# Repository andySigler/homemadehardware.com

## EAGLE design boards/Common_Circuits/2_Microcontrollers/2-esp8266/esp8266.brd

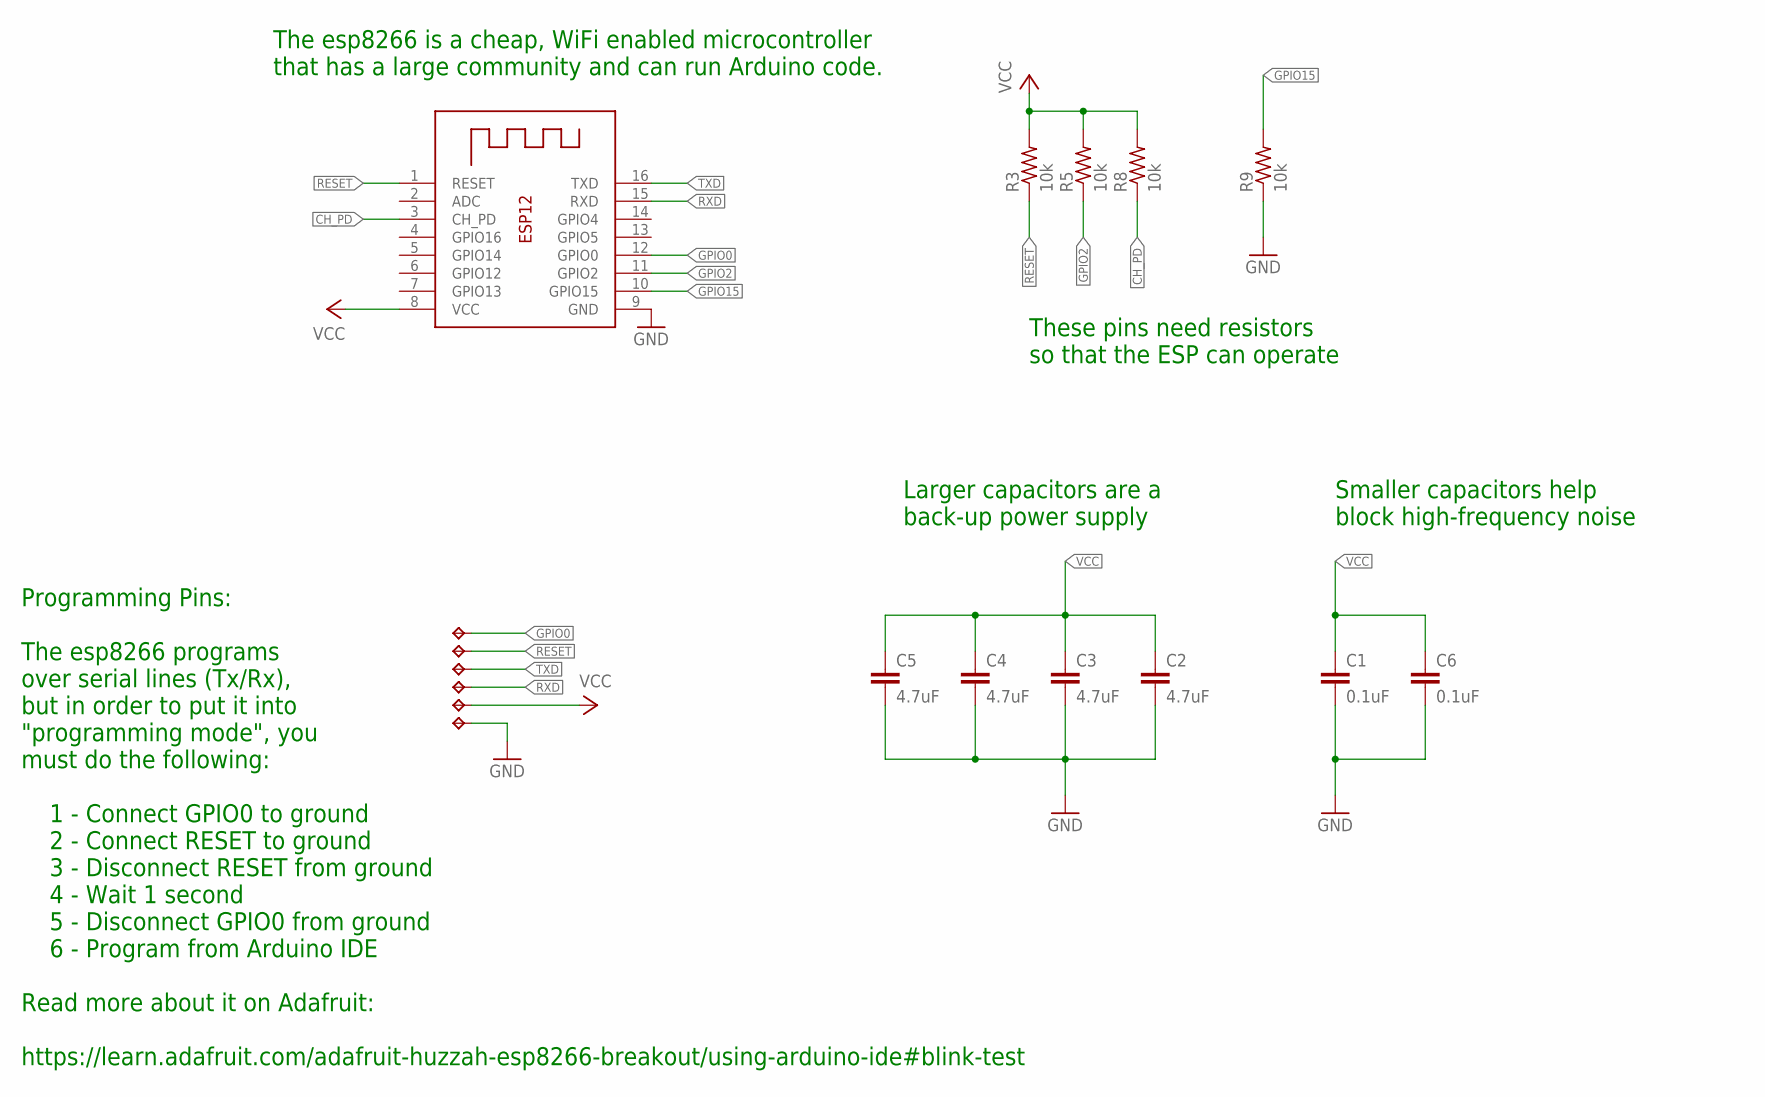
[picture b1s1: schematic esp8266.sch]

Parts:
C1, C6: 0.1uF; 0603
C2, C3, C4, C5: 4.7uF; 0603
GND: TPTP20R; TP20R
GPIO0: TPTP20R; TP20R
R3, R5, R8, R9: 10k; R0603
RESET: TPTP20R; TP20R
RX: TPTP20R; TP20R
TX: TPTP20R; TP20R
VCC: TPTP20R; TP20R
X1: ESP-12

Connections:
CH_PD: R8.1, X1.3 (CH_PD)
GND: C1.2, C2.2, C3.2, C4.2, C5.2, C6.2, GND.TP, R9.1, X1.9 (GND)
GPIO0: GPIO0.TP, X1.12 (GPIO0)
GPIO2: R5.1, X1.11 (GPIO2)
GPIO15: R9.2, X1.10 (GPIO15)
RESET: R3.1, RESET.TP, X1.1 (RESET)
RXD: RX.TP, X1.15 (RXD)
TXD: TX.TP, X1.16 (TXD)
VCC: C1.1, C2.1, C3.1, C4.1, C5.1, C6.1, R3.2, R5.2, R8.2, VCC.TP, X1.8 (VCC)

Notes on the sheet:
These pins need resistors so that the ESP can operate
The esp8266 is a cheap, WiFi enabled microcontroller that has a large community and can run Arduino code.
Programming Pins: The esp8266 programs over serial lines (Tx/Rx), but in order to put it into "programming mode", you must do the following: 1 - Connect GPIO0 to ground 2 - Connect RESET to ground 3 - Disconnect RESET from ground 4 - Wait 1 second 5 - Disconnect GPIO0 from ground 6 - Program from A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
Smaller capacitors help block high-frequency noise
Larger capacitors are a back-up power supply

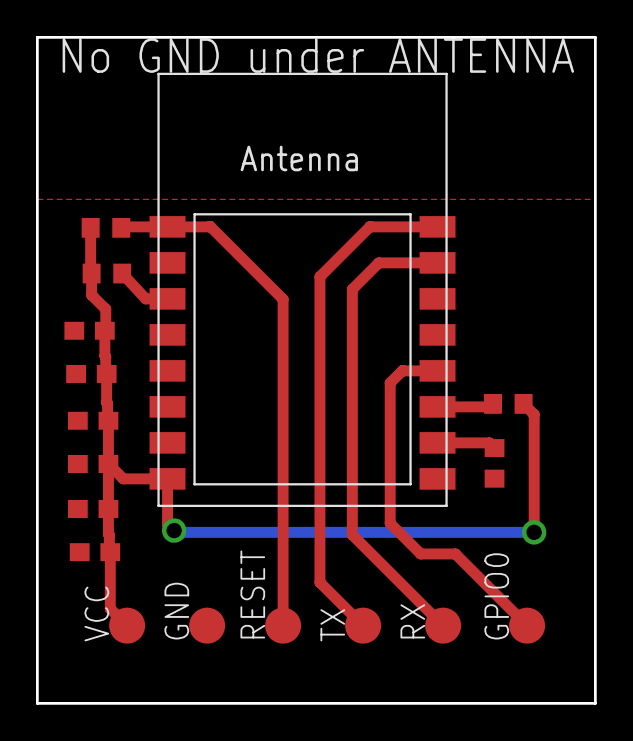
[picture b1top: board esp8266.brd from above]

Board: 2 copper layers, 31.0 x 37.0 mm, 17 parts (0 on the bottom side), 9 nets.

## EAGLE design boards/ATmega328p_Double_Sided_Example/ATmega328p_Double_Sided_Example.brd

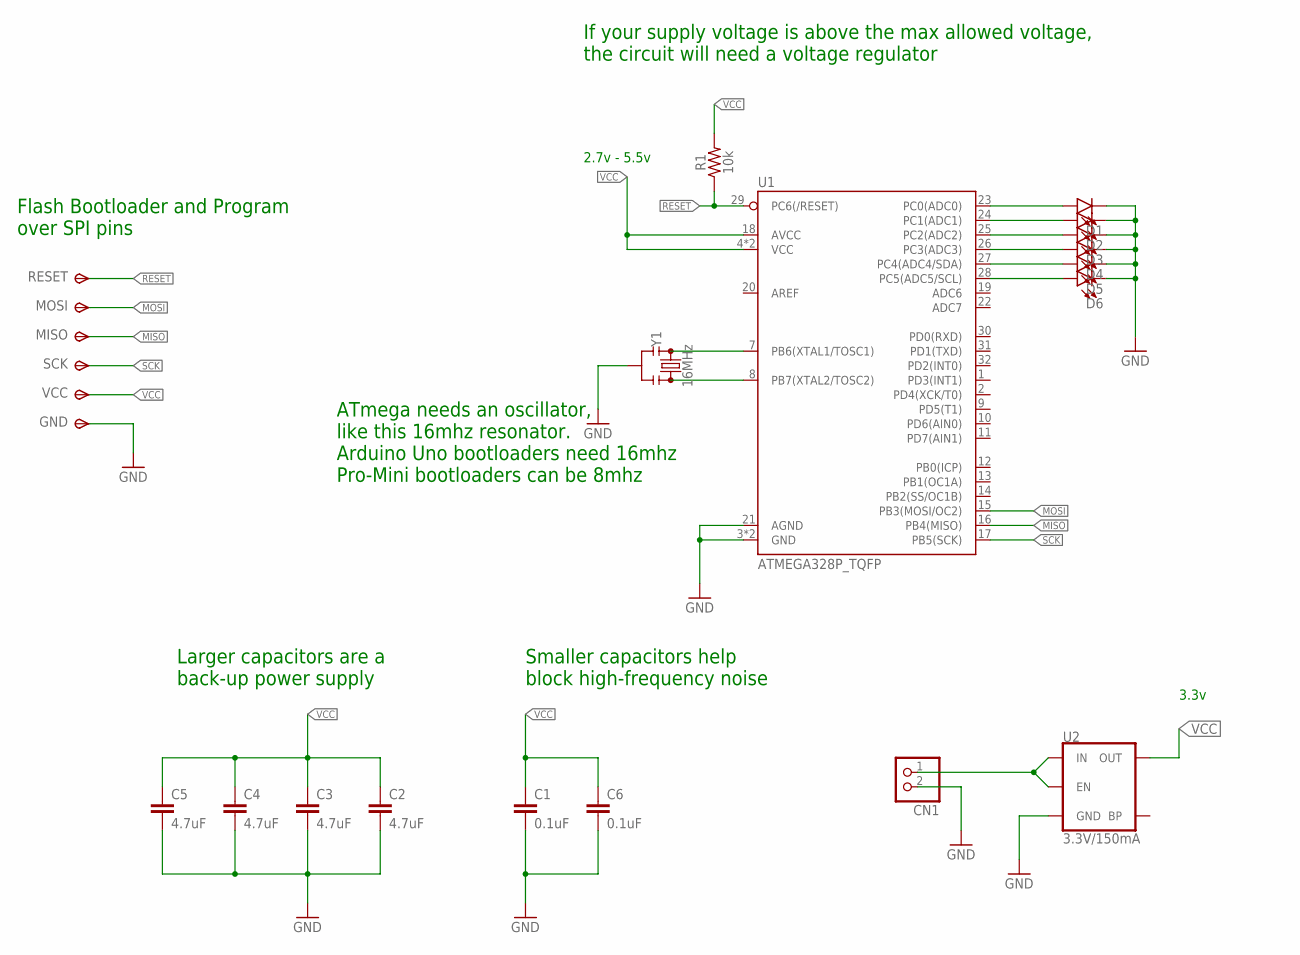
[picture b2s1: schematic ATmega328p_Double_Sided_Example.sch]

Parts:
C1, C6: 0.1uF; 0603
C2, C3, C4, C5: 4.7uF; 0603
CN1: JST_2PIN-SMT-RA; JST-PH-2-SMT-RA
D1, D2, D3, D4, D5, D6: LED0603; LED-0603
GND: TPSTP14SQ; TP14SQ
MISO: TPSTP14SQ; TP14SQ
MOSI: TPSTP14SQ; TP14SQ
R1: 10k; 0603
RESET: TPSTP14SQ; TP14SQ
SCK: TPSTP14SQ; TP14SQ
U1: ATMEGA328P_TQFP; TQFP32-08
U2: 3.3V/150mA; SOT23-5
VCC: TPSTP14SQ; TP14SQ
Y1: 16MHz; RESONATOR-SMD-3.2X1.3

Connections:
GND: C1.2, C2.2, C3.2, C4.2, C5.2, C6.2, CN1.2 (1), D1.C, D2.C, D3.C, D4.C, D5.C, D6.C, GND.TP, U1.3 (GND), U1.5 (GND), U1.21 (AGND), U2.2 (GND), Y1.2
MISO: MISO.TP, U1.16 (PB4(MISO))
MOSI: MOSI.TP, U1.15 (PB3(MOSI/OC2))
unnamed: CN1.1 (2), U2.1 (IN), U2.3 (EN)
unnamed: U1.7 (PB6(XTAL1/TOSC1)), Y1.1
unnamed: U1.8 (PB7(XTAL2/TOSC2)), Y1.3
unnamed: D1.A, U1.23 (PC0(ADC0))
unnamed: D2.A, U1.24 (PC1(ADC1))
unnamed: D3.A, U1.25 (PC2(ADC2))
unnamed: D4.A, U1.26 (PC3(ADC3))
unnamed: D5.A, U1.27 (PC4(ADC4/SDA))
unnamed: D6.A, U1.28 (PC5(ADC5/SCL))
RESET: R1.1, RESET.TP, U1.29 (PC6(/RESET))
SCK: SCK.TP, U1.17 (PB5(SCK))
VCC: C1.1, C2.1, C3.1, C4.1, C5.1, C6.1, R1.2, U1.4 (VCC), U1.6 (VCC), U1.18 (AVCC), U2.5 (OUT), VCC.TP

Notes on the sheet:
2.7v - 5.5v
Flash Bootloader and Program over SPI pins
If your supply voltage is above the max allowed voltage, the circuit will need a voltage regulator
Smaller capacitors help block high-frequency noise
Larger capacitors are a back-up power supply
ATmega needs an oscillator, like this 16mhz resonator. Arduino Uno bootloaders need 16mhz Pro-Mini bootloaders can be 8mhz
3.3v

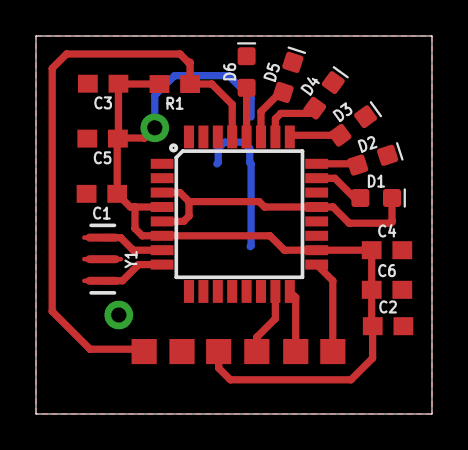
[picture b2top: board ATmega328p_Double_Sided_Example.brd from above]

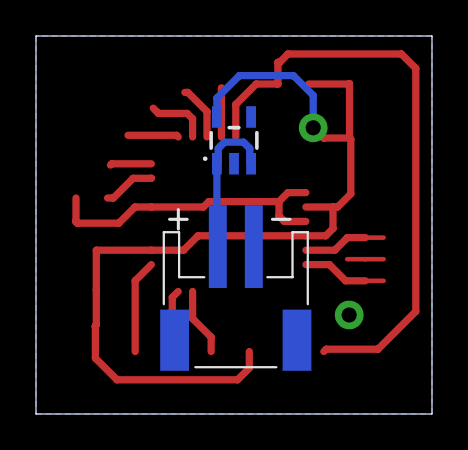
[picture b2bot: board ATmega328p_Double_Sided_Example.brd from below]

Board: 2 copper layers, 22.0 x 21.0 mm, 23 parts (2 on the bottom side), 15 nets.

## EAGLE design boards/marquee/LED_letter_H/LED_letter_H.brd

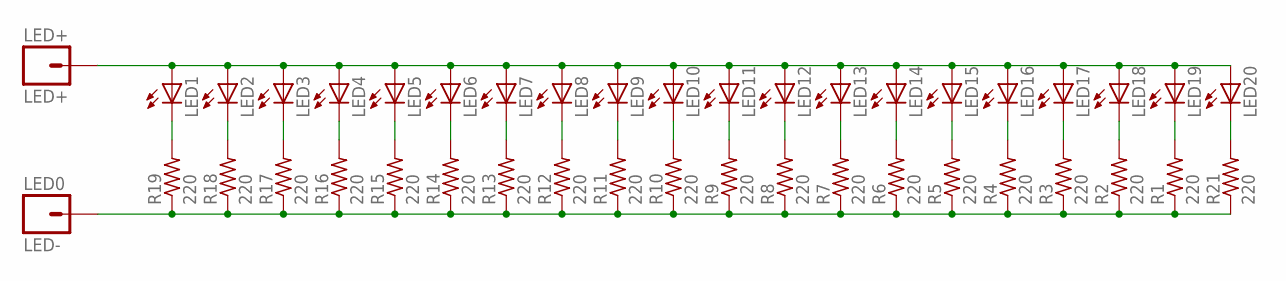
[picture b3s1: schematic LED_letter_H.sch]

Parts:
LED0: LED-; 1X01_OFFSET
LED1, LED2, LED3, LED4, LED5, LED6, LED7, LED8, LED9, LED10, LED11, LED12, LED13, LED14, LED15, LED16, LED17, LED18, LED19, LED20: LED5MM
LED+: LED+; 1X01_OFFSET
R1, R2, R3, R4, R5, R6, R7, R8, R9, R10, R11, R12, R13, R14, R15, R16, R17, R18, R19, R21: 220; 0207/10

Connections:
+: LED1.A, LED2.A, LED3.A, LED4.A, LED5.A, LED6.A, LED7.A, LED8.A, LED9.A, LED10.A, LED11.A, LED12.A, LED13.A, LED14.A, LED15.A, LED16.A, LED17.A, LED18.A, LED19.A, LED20.A, LED+.1
-: LED0.1, R1.1, R2.1, R3.1, R4.1, R5.1, R6.1, R7.1, R8.1, R9.1, R10.1, R11.1, R12.1, R13.1, R14.1, R15.1, R16.1, R17.1, R18.1, R19.1, R21.1
unnamed: LED1.K (C), R19.2
unnamed: LED20.K (C), R21.2
unnamed: LED19.K (C), R1.2
unnamed: LED18.K (C), R2.2
unnamed: LED17.K (C), R3.2
unnamed: LED16.K (C), R4.2
unnamed: LED15.K (C), R5.2
unnamed: LED14.K (C), R6.2
unnamed: LED13.K (C), R7.2
unnamed: LED12.K (C), R8.2
unnamed: LED11.K (C), R9.2
unnamed: LED10.K (C), R10.2
unnamed: LED9.K (C), R11.2
unnamed: LED8.K (C), R12.2
unnamed: LED7.K (C), R13.2
unnamed: LED6.K (C), R14.2
unnamed: LED5.K (C), R15.2
unnamed: LED4.K (C), R16.2
unnamed: LED3.K (C), R17.2
unnamed: LED2.K (C), R18.2

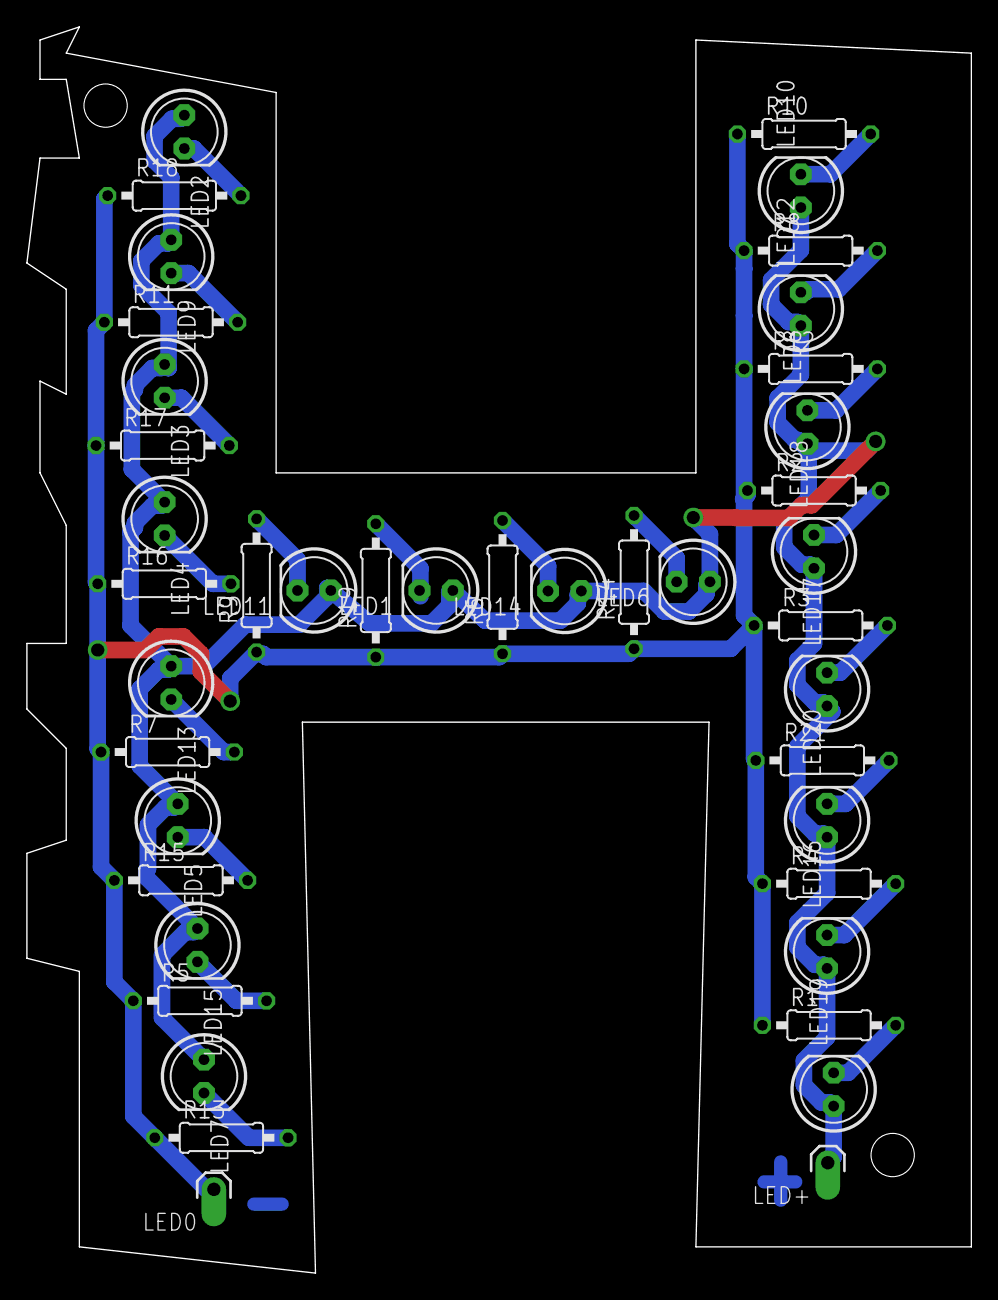
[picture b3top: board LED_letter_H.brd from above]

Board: 2 copper layers, 72.0 x 95.0 mm, 42 parts (0 on the bottom side), 22 nets.

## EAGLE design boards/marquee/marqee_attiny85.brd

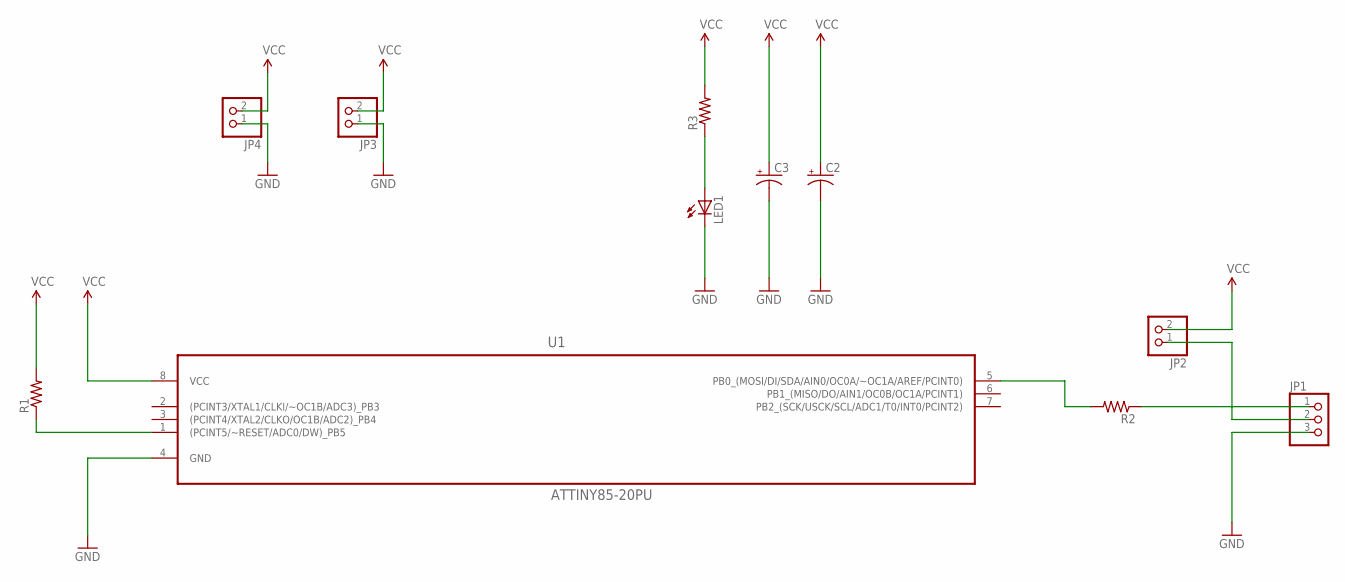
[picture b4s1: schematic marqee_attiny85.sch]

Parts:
C2, C3: CPOL-USE5-8.5; E5-8,5
JP1: PINHD-1X3; 1X03
JP2, JP3, JP4: PINHD-1X2; 1X02
LED1: LED5MM
R1, R2, R3: R-US_0207/10; 0207/10
U1: ATTINY85-20PU; DIP254P762X533-8

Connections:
GND: C2.-, C3.-, JP1.3, JP3.1, JP4.1, LED1.K (C), U1.4 (GND)
unnamed: R1.1, U1.1 ((PCINT5/~RESET/ADC0/DW)_PB5)
unnamed: JP1.1, R2.1
unnamed: LED1.A, R3.1
unnamed: R2.2, U1.5 (PB0_(MOSI/DI/SDA/AIN0/OC0A/~OC1A/AREF/P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)
unnamed: JP1.2, JP2.1
VCC: C2.+, C3.+, JP2.2, JP3.2, JP4.2, R1.2, R3.2, U1.8 (VCC)

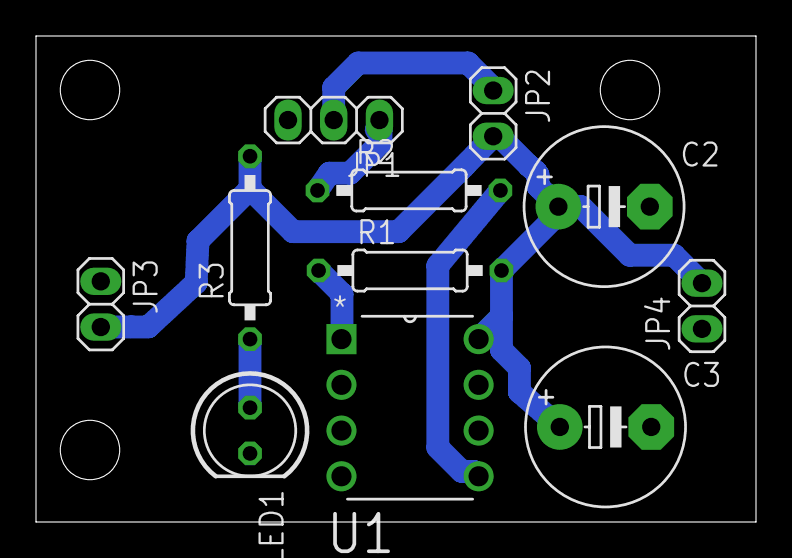
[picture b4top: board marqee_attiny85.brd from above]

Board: 2 copper layers, 40.0 x 27.0 mm, 11 parts (0 on the bottom side), 7 nets.

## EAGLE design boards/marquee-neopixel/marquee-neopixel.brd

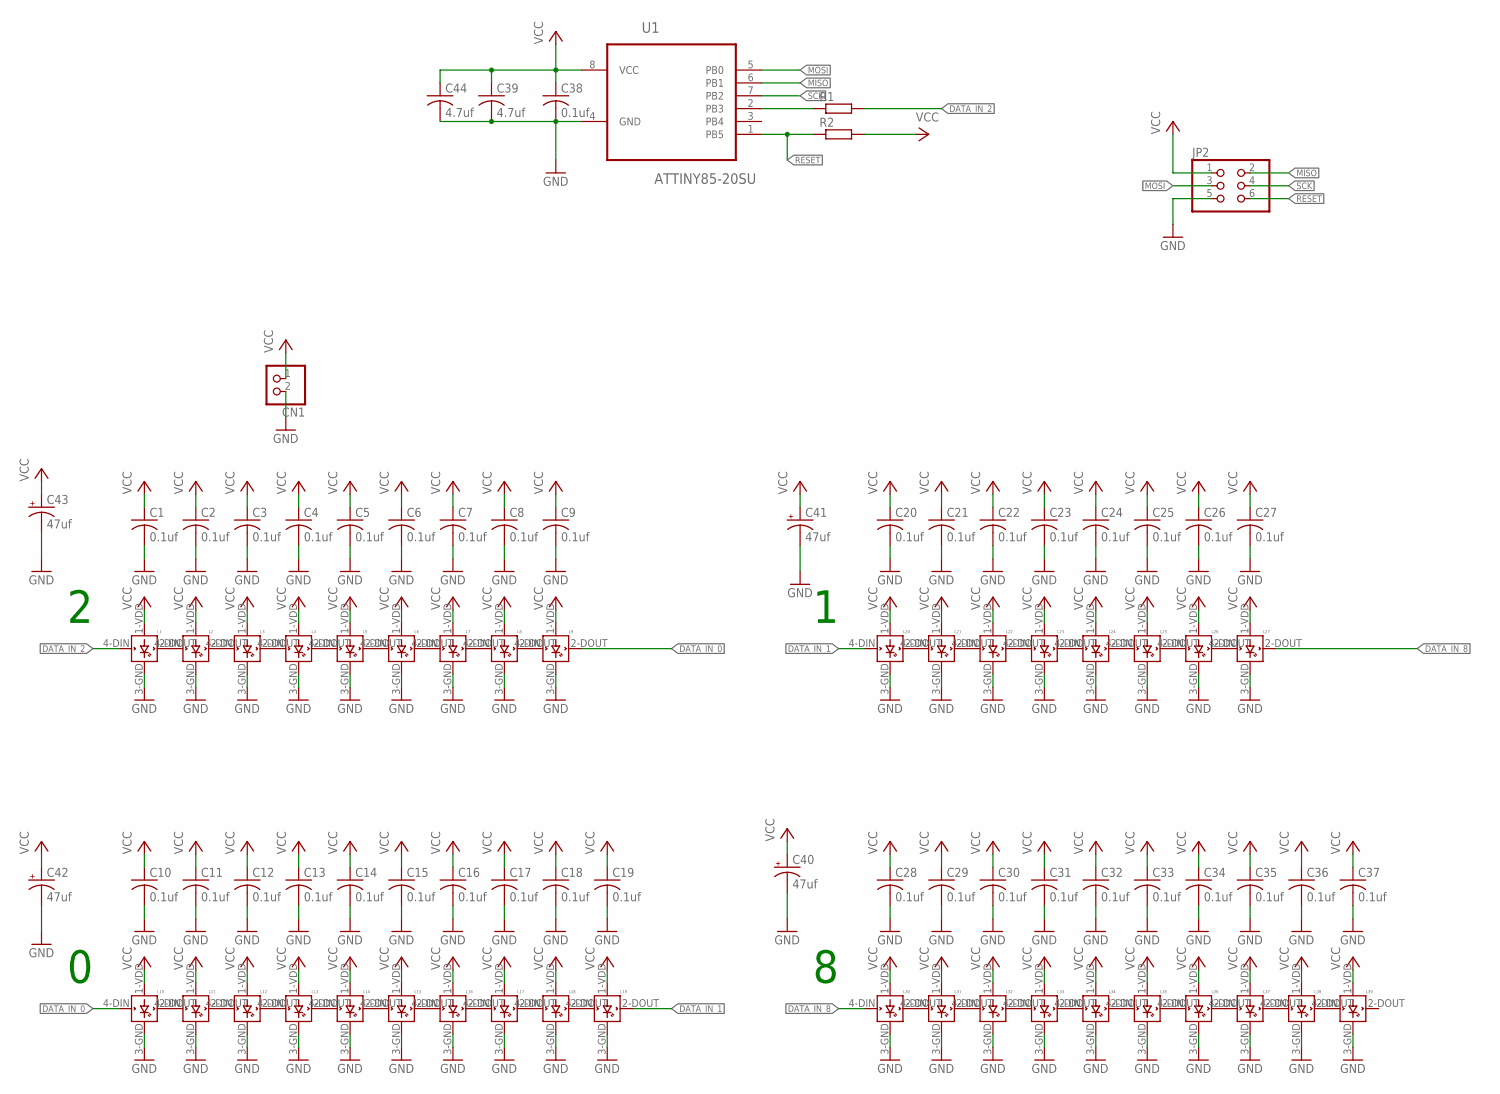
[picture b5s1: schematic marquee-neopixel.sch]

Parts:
C1, C2, C3, C4, C5, C6, C7, C8, C9, C10, C11, C12, C13, C14, C15, C16, C17, C18, C19, C20, C21, C22, C23, C24, C25, C26, C27, C28, C29, C30, C31, C32, C33, C34, C35, C36, C37, C38: 0.1uf; C0603
C39, C44: 4.7uf; C0603
C40, C41, C42, C43: 47uf; 153CLV-0605
CN1: JST_2PIN-SMT-RA; JST-PH-2-SMT-RA
JP2: PINHD-2X3; 2X03
L1, L2, L3, L4, L5, L6, L7, L8, L9, L10, L11, L12, L13, L14, L15, L16, L17, L18, L19, L20, L21, L22, L23, L24, L25, L26, L27, L30, L31, L32, L33, L34, L35, L36, L37, L38, L39: WS2812B
R1, R2: RR0603; R0603
U1: ATTINY85-20SU; SOIC127P798X216-8N

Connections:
DATA_IN_0: L9.2-DOUT (DOUT), L10.4-DIN (DIN)
DATA_IN_1: L19.2-DOUT (DOUT), L20.4-DIN (DIN)
DATA_IN_2: L1.4-DIN (DIN), R1.2
DATA_IN_8: L27.2-DOUT (DOUT), L30.4-DIN (DIN)
GND: C1.2, C2.2, C3.2, C4.2, C5.2, C6.2, C7.2, C8.2, C9.2, C10.2, C11.2, C12.2, C13.2, C14.2, C15.2, C16.2, C17.2, C18.2, C19.2, C20.2, C21.2, C22.2, C23.2, C24.2, C25.2, C26.2, C27.2, C28.2, C29.2, C30.2, C31.2, C32.2, C33.2, C34.2, C35.2, C36.2, C37.2, C38.2, C39.2, C40.-, C41.-, C42.-, C43.-, C44.2, CN1.2 (1), JP2.5, L1.3-GND (GND), L2.3-GND (GND), L3.3-GND (GND), L4.3-GND (GND), L5.3-GND (GND), L6.3-GND (GND), L7.3-GND (GND), L8.3-GND (GND), L9.3-GND (GND), L10.3-GND (GND), L11.3-GND (GND), L12.3-GND (GND), L13.3-GND (GND), L14.3-GND (GND), L15.3-GND (GND), L16.3-GND (GND), L17.3-GND (GND), L18.3-GND (GND), L19.3-GND (GND), L20.3-GND (GND), L21.3-GND (GND), L22.3-GND (GND), L23.3-GND (GND), L24.3-GND (GND), L25.3-GND (GND), L26.3-GND (GND), L27.3-GND (GND), L30.3-GND (GND), L31.3-GND (GND), L32.3-GND (GND), L33.3-GND (GND), L34.3-GND (GND), L35.3-GND (GND), L36.3-GND (GND), L37.3-GND (GND), L38.3-GND (GND), L39.3-GND (GND), U1.4 (GND)
MISO: JP2.2, U1.6 (PB1)
MOSI: JP2.3, U1.5 (PB0)
unnamed: L1.2-DOUT (DOUT), L2.4-DIN (DIN)
unnamed: L2.2-DOUT (DOUT), L3.4-DIN (DIN)
unnamed: L3.2-DOUT (DOUT), L4.4-DIN (DIN)
unnamed: L4.2-DOUT (DOUT), L5.4-DIN (DIN)
unnamed: L5.2-DOUT (DOUT), L6.4-DIN (DIN)
unnamed: L6.2-DOUT (DOUT), L7.4-DIN (DIN)
unnamed: L7.2-DOUT (DOUT), L8.4-DIN (DIN)
unnamed: L8.2-DOUT (DOUT), L9.4-DIN (DIN)
unnamed: L10.2-DOUT (DOUT), L11.4-DIN (DIN)
unnamed: L11.2-DOUT (DOUT), L12.4-DIN (DIN)
unnamed: L12.2-DOUT (DOUT), L13.4-DIN (DIN)
unnamed: L13.2-DOUT (DOUT), L14.4-DIN (DIN)
unnamed: L14.2-DOUT (DOUT), L15.4-DIN (DIN)
unnamed: L15.2-DOUT (DOUT), L16.4-DIN (DIN)
unnamed: L16.2-DOUT (DOUT), L17.4-DIN (DIN)
unnamed: L17.2-DOUT (DOUT), L18.4-DIN (DIN)
unnamed: L18.2-DOUT (DOUT), L19.4-DIN (DIN)
unnamed: L20.2-DOUT (DOUT), L21.4-DIN (DIN)
unnamed: L21.2-DOUT (DOUT), L22.4-DIN (DIN)
unnamed: L22.2-DOUT (DOUT), L23.4-DIN (DIN)
unnamed: L23.2-DOUT (DOUT), L24.4-DIN (DIN)
unnamed: L24.2-DOUT (DOUT), L25.4-DIN (DIN)
unnamed: L25.2-DOUT (DOUT), L26.4-DIN (DIN)
unnamed: L26.2-DOUT (DOUT), L27.4-DIN (DIN)
unnamed: R1.1, U1.2 (PB3)
unnamed: L30.2-DOUT (DOUT), L31.4-DIN (DIN)
unnamed: L31.2-DOUT (DOUT), L32.4-DIN (DIN)
unnamed: L32.2-DOUT (DOUT), L33.4-DIN (DIN)
unnamed: L33.2-DOUT (DOUT), L34.4-DIN (DIN)
unnamed: L34.2-DOUT (DOUT), L35.4-DIN (DIN)
unnamed: L35.2-DOUT (DOUT), L36.4-DIN (DIN)
unnamed: L36.2-DOUT (DOUT), L37.4-DIN (DIN)
unnamed: L37.2-DOUT (DOUT), L38.4-DIN (DIN)
unnamed: L38.2-DOUT (DOUT), L39.4-DIN (DIN)
RESET: JP2.6, R2.1, U1.1 (PB5)
SCK: JP2.4, U1.7 (PB2)
VCC: C1.1, C2.1, C3.1, C4.1, C5.1, C6.1, C7.1, C8.1, C9.1, C10.1, C11.1, C12.1, C13.1, C14.1, C15.1, C16.1, C17.1, C18.1, C19.1, C20.1, C21.1, C22.1, C23.1, C24.1, C25.1, C26.1, C27.1, C28.1, C29.1, C30.1, C31.1, C32.1, C33.1, C34.1, C35.1, C36.1, C37.1, C38.1, C39.1, C40.+, C41.+, C42.+, C43.+, C44.1, CN1.1 (2), JP2.1, L1.1-VDD (VDD), L2.1-VDD (VDD), L3.1-VDD (VDD), L4.1-VDD (VDD), L5.1-VDD (VDD), L6.1-VDD (VDD), L7.1-VDD (VDD), L8.1-VDD (VDD), L9.1-VDD (VDD), L10.1-VDD (VDD), L11.1-VDD (VDD), L12.1-VDD (VDD), L13.1-VDD (VDD), L14.1-VDD (VDD), L15.1-VDD (VDD), L16.1-VDD (VDD), L17.1-VDD (VDD), L18.1-VDD (VDD), L19.1-VDD (VDD), L20.1-VDD (VDD), L21.1-VDD (VDD), L22.1-VDD (VDD), L23.1-VDD (VDD), L24.1-VDD (VDD), L25.1-VDD (VDD), L26.1-VDD (VDD), L27.1-VDD (VDD), L30.1-VDD (VDD), L31.1-VDD (VDD), L32.1-VDD (VDD), L33.1-VDD (VDD), L34.1-VDD (VDD), L35.1-VDD (VDD), L36.1-VDD (VDD), L37.1-VDD (VDD), L38.1-VDD (VDD), L39.1-VDD (VDD), R2.2, U1.8 (VCC)

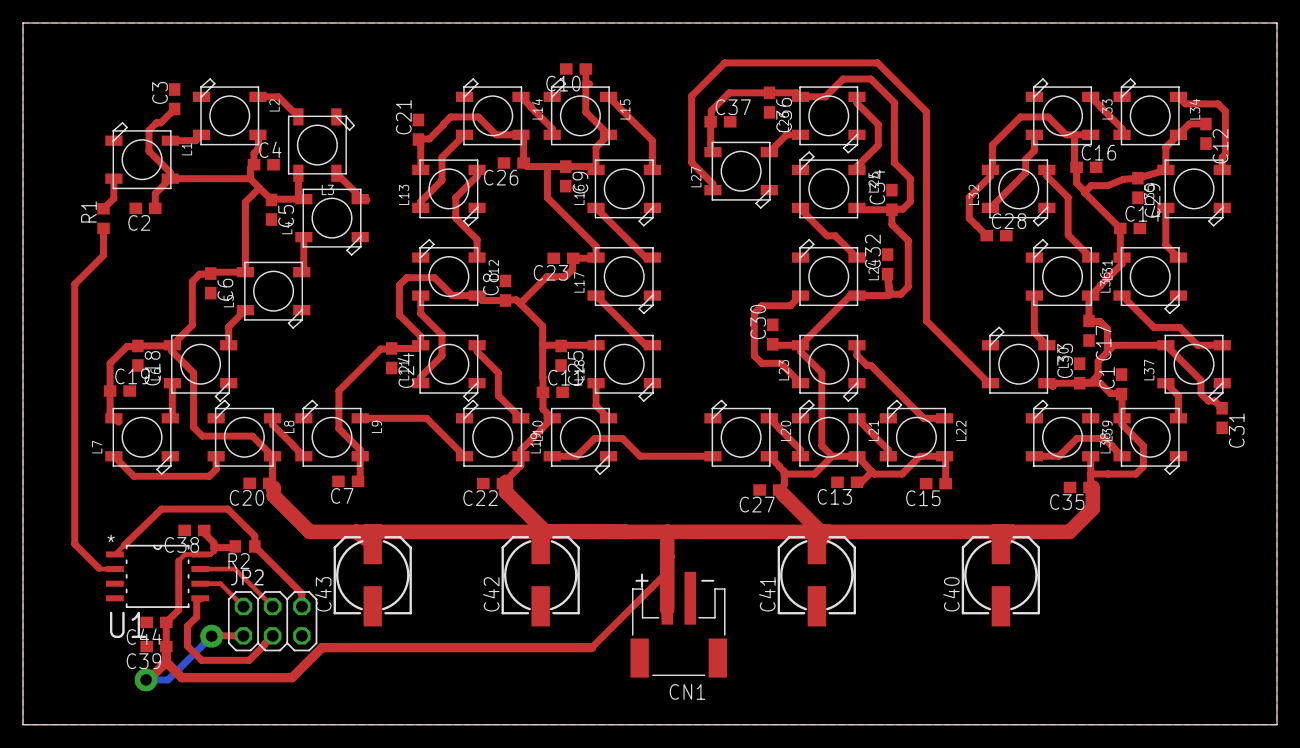
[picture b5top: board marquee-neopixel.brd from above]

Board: 2 copper layers, 109.0 x 61.0 mm, 86 parts (0 on the bottom side), 44 nets.

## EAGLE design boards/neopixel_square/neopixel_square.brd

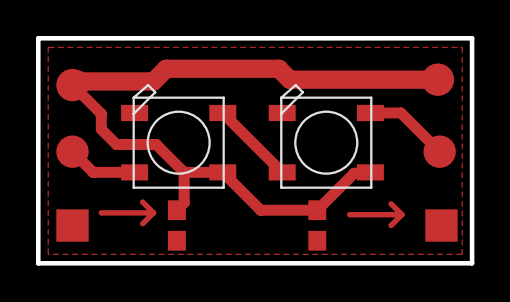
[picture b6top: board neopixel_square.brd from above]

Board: 2 copper layers, 24.1 x 12.5 mm, 10 parts (0 on the bottom side), 5 nets.

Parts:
C1, C9: 0.1uf; C0603
DATA, DATA1: TPTP18R; TP18R
GND: TPTP18SQ; TP18SQ
GROUND: TPTP18R; TP18R
L1, L9: WS2812B
POWER: TPTP18SQ; TP18SQ
VCC: TPTP18R; TP18R

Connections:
DATA_IN: DATA.TP, L9.4-DIN
DATA_OUT: DATA1.TP, L1.2-DOUT
GND: C1.2, C9.2, GND.TP, L1.3-GND, L9.3-GND, POWER.TP
unnamed: L1.4-DIN, L9.2-DOUT
VCC: C1.1, C9.1, GROUND.TP, L1.1-VDD, L9.1-VDD, VCC.TP

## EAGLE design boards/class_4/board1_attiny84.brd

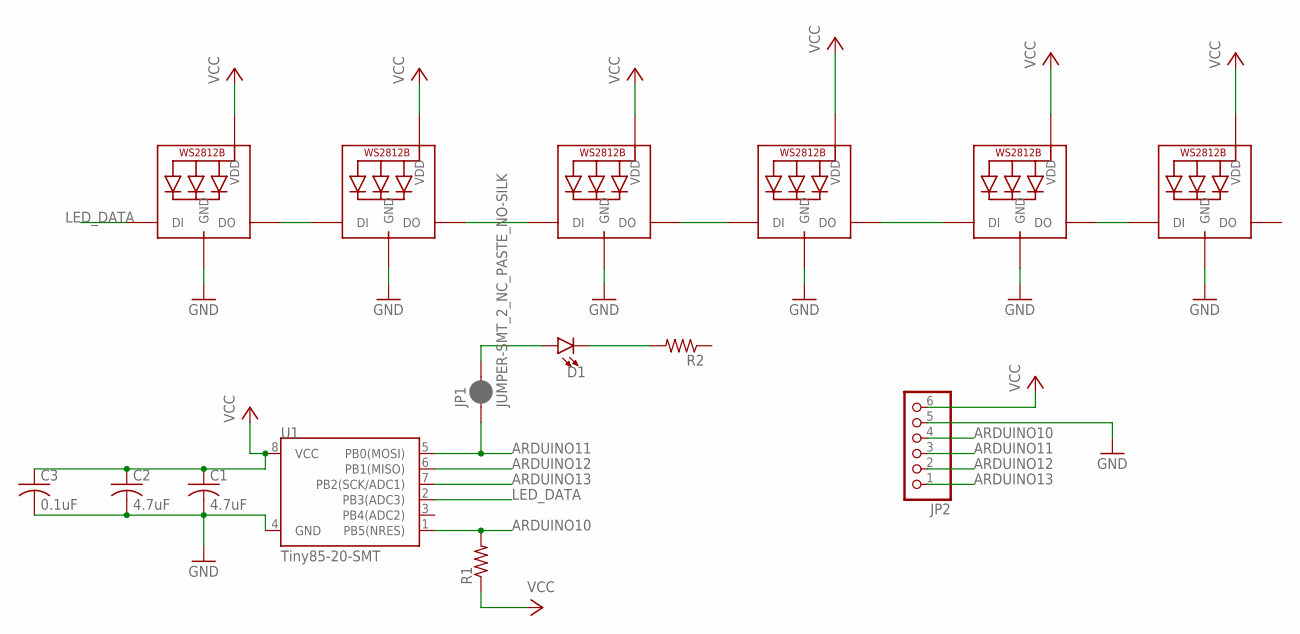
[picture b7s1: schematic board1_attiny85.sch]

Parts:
C1, C2: 4.7uF; C0603
C3: 0.1uF; C0603
D1: LED0603; LED-0603
JP1: JUMPER-SMT_2_NC_PASTE_NO-SILK; SMT-JUMPER_2_NC_PASTE_NO-SILK
JP2: PINHD-1X6; 1X06
LED1, LED2, LED3, LED4, LED5, LED6: WS2812B5050; WS2812B
R1, R2: R-US_R0603; R0603
U1: Tiny85-20-SMT; SO08-EIAJ_MCU

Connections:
ARDUINO10: JP2.4, R1.2, U1.1 (PB5(NRES))
ARDUINO11: JP1.1, JP2.3, U1.5 (PB0(MOSI))
ARDUINO12: JP2.2, U1.6 (PB1(MISO))
ARDUINO13: JP2.1, U1.7 (PB2(SCK/ADC1))
GND: C1.2, C2.2, C3.2, JP2.5, LED1.3-GND (GND), LED2.3-GND (GND), LED3.3-GND (GND), LED4.3-GND (GND), LED5.3-GND (GND), LED6.3-GND (GND), U1.4 (GND)
LED_DATA: LED1.4-DIN (DI), U1.2 (PB3(ADC3))
unnamed: LED1.2-DOUT (DO), LED2.4-DIN (DI)
unnamed: D1.C, R2.2
unnamed: D1.A, JP1.2
unnamed: LED2.2-DOUT (DO), LED3.4-DIN (DI)
unnamed: LED3.2-DOUT (DO), LED4.4-DIN (DI)
unnamed: LED4.2-DOUT (DO), LED5.4-DIN (DI)
unnamed: LED5.2-DOUT (DO), LED6.4-DIN (DI)
VCC: C1.1, C2.1, C3.1, JP2.6, LED1.1-VDD (VDD), LED2.1-VDD (VDD), LED3.1-VDD (VDD), LED4.1-VDD (VDD), LED5.1-VDD (VDD), LED6.1-VDD (VDD), R1.1, U1.8 (VCC)

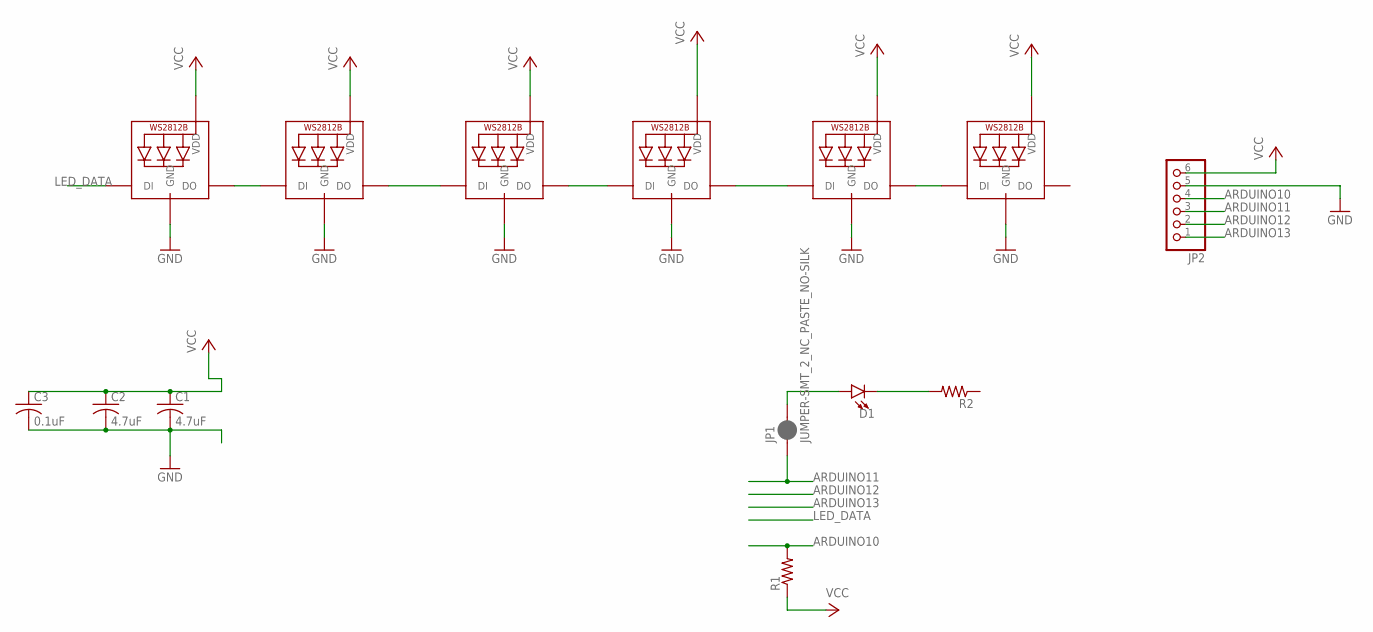
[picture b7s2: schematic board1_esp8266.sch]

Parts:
C1, C2: 4.7uF; C0603
C3: 0.1uF; C0603
D1: LED0603; LED-0603
JP1: JUMPER-SMT_2_NC_PASTE_NO-SILK; SMT-JUMPER_2_NC_PASTE_NO-SILK
JP2: PINHD-1X6; 1X06
LED1, LED2, LED3, LED4, LED5, LED6: WS2812B5050; WS2812B
R1, R2: R-US_R0603; R0603

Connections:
ARDUINO10: JP2.4, R1.2; also elsewhere on the board
ARDUINO11: JP1.1, JP2.3; also elsewhere on the board
ARDUINO12: JP2.2; also elsewhere on the board
ARDUINO13: JP2.1; also elsewhere on the board
GND: C1.2, C2.2, C3.2, JP2.5, LED1.3-GND (GND), LED2.3-GND (GND), LED3.3-GND (GND), LED4.3-GND (GND), LED5.3-GND (GND), LED6.3-GND (GND); also elsewhere on the board
LED_DATA: LED1.4-DIN (DI); also elsewhere on the board
unnamed: LED1.2-DOUT (DO), LED2.4-DIN (DI)
unnamed: D1.C, R2.2
unnamed: D1.A, JP1.2
unnamed: LED2.2-DOUT (DO), LED3.4-DIN (DI)
unnamed: LED3.2-DOUT (DO), LED4.4-DIN (DI)
unnamed: LED4.2-DOUT (DO), LED5.4-DIN (DI)
unnamed: LED5.2-DOUT (DO), LED6.4-DIN (DI)
VCC: C1.1, C2.1, C3.1, JP2.6, LED1.1-VDD (VDD), LED2.1-VDD (VDD), LED3.1-VDD (VDD), LED4.1-VDD (VDD), LED5.1-VDD (VDD), LED6.1-VDD (VDD), R1.1; also elsewhere on the board

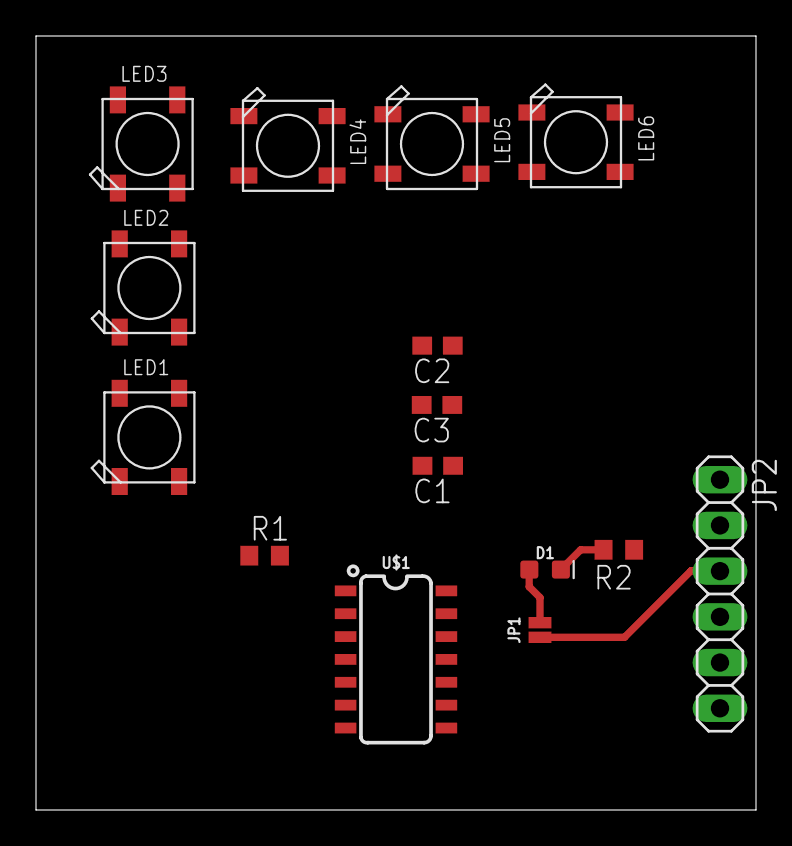
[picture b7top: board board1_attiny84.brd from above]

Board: 2 copper layers, 40.0 x 43.0 mm, 15 parts (0 on the bottom side), 11 nets.

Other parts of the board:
U$1: ATTINY84; SO14

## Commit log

2015-08-01 init commit
2015-08-01 added basic layout
2015-08-05 small updates before showing tom
2015-08-05 adsf
2015-08-09 reformatting and added lots of links
2015-08-09 asdf
2015-08-10 more content added to syllabus page
2015-08-13 updated Links page, maybe it's done
2015-08-13 added overview to syllabus page
2015-08-16 added prior projects and more stuff
2015-08-29 added more info to syllabus page
2015-08-29 created Examples page
2015-09-03 final update before class starts
2015-09-03 fixed andy's link
2015-09-04 added board manager links
2015-09-04 changed linked soldering iron to a cheaper one
2015-09-10 added student links, and fixed misspelled word
2015-09-10 added tinkersphere link
2015-09-10 added links to Eagle libraries
2015-09-10 new student link
2015-09-10 added more student links
2015-09-14 added eagle commands page
2015-09-14 updated students page
2015-09-22 removed waitlist student, and added board commands
2015-09-24 added vimeo tutorials to the links page
2015-09-24 updated dynamask link to be an eBay search term
2015-10-01 changed syllabus for class 5
2015-10-12 added new Processes page
2015-10-13 fixed heat gun temperature
2015-10-15 added roland to class 7 and processes page
2015-10-16 added new bit buying links to things page
2015-10-29 updated syllabus
2015-11-11 added new job to index and about pages
2015-11-13 updated links page to include wireless modules
2015-11-13 added PNP ulp to links folder
2015-12-03 small change
2017-01-23 adds .gitignore
2017-01-23 adds archives to hold 2015 class pages
2017-01-23 prepares website for Spring 2017 class
2017-01-24 starts adding lesson plans to each class on syllabus
2017-01-25 adds details to classes on syllabus page
2017-01-27 updates Things page with required tools to order
2017-01-27 adds archive html page and nav links
2017-01-27 adds link to examples from Michelle's course
2017-01-27 adds link to 8mhz internal board
2017-01-28 updates students page
2017-01-28 adds list of options for ordering out
2017-01-29 udates week 1 homework assignment
2017-01-29 add linkable ids to weeks
2017-01-29 fixes links
2017-01-29 adds PCB soldering video ink
2017-01-29 different solding link
2017-01-29 fixes links on old Examples page
2017-01-30 adds student link
2017-01-30 adds Common Sub-Circuits
2017-01-30 adds link to parts search engine
2017-02-03 updates some blog links
2017-02-03 adds missing student links
2017-02-04 updates class 2 homework, and updates eagle commands page
2017-02-04 adds video to syllabus page
2017-02-10 adds example boards for class 3
2017-02-10 udpdates student links
2017-02-10 updates example board to use pot
2017-02-11 adds class 3 video and updates drill bit link
2017-02-17 updates class 4 topics
2017-03-03 updates classes for after reschedule
2017-03-09 update syllabus activities
2017-03-24 update for class 7
2017-03-31 adds class recording to class 7
2017-03-31 updates class 9 to monday
2018-01-22 moves 2017 class to archive; creates blank 2018 syllabus
2018-01-28 adds class material for week 1
2018-01-28 adds 3 student blog links
2018-01-28 students without links are red
2018-02-03 updates after class 2
2018-02-12 class 3 materials; adds Arrow-NeoPixel PCB
2018-02-23 adds material for class 4
2018-02-24 more stuff for class 4
2018-04-02 adds example boards for common circuits
2018-04-05 adds ESP8266 board to common circuits
2018-04-05 adds REgulators example to common circuits
2019-03-22 reorganizing; adds header imeages for classes
2019-03-23 finishes header images; updates tools/materials links; adds guides page
2019-03-25 adds student names
2019-03-25 adds guide for ATtiny85
2019-03-25 remove link to non-existant jig guide
2019-04-02 working on guide for eagle
2019-04-02 final change before class 2
2019-04-02 adds link to repo on syllabus page
2019-04-02 adds parts placement image for lipo board
2019-04-02 creates eagle setup guide page
2019-04-02 finishes eagle board design 1 guide
2019-04-02 adds link to marquee phrase doc
2019-04-02 adds two more student links
2019-04-03 fixes lipo LED image
2019-04-05 fixes student blog link
2019-04-05 creates placeholders for more guides on milling, reflow, and schematics
2019-04-08 adds text, images, and video for bantam setup guide
2019-04-08 finishes bantam-setup, bantam-1, and schematic guides
2019-04-09 adds one more link
2019-04-09 adds smd soldering guide; prep for class 3
2019-04-15 adds templates for future guides; finishes eagle schematic 2 guide
2019-04-15 add schematic-2 images
2019-04-15 completes eagle-board-design-2 guide
2019-04-15 starting rec-parts guide
2019-04-16 finishes guide on rec parts
2019-04-16 removes nrf52 link from rec parts guide
2019-04-22 adds guide for redesigining open source schematics
2019-04-23 adds guides links and homework for classes 4 and 5
2019-04-23 fixes id name on atsamd11 recommended part
2019-04-23 adds final student blog link
2019-04-23 adds desc to lass 5 section B
2019-04-25 change home screen to about page; create syllabus section; add a few guides
2019-04-25 adds eagle library guide
2019-04-25 adds link to intro of library guide
2019-04-25 reverts nav structure to syllabus as home
2019-04-27 adds most of stencil guide, still missing images for milling
2019-04-29 adds a bit more context to the stencil milling section
2019-05-03 removes mentions of bug about SVG; save SVG as version 1.0
2019-05-05 fixes broken link to image
2019-05-05 adds header images for guides
2019-05-05 copies summaries from guides
2019-05-05 increase header height; add guide summary at top
2019-05-05 adds header images to guide pages
2019-05-10 arduino uno guides done; moves guides to homepage
2019-05-19 adds top-link for personal website; make website title link to homepage
2019-05-21 don't display link
2019-10-22 moves 2019 webpages to archives folder
2019-10-22 initial 2020 syllabus and webpages
2019-10-22 corrects to Students 2020
2019-12-24 adds assignment page for marquee sign
2019-12-28 updates eagle setup guide
2020-01-31 changes photocell to phototransistor name
2020-01-31 updates things page for 2020
2020-01-31 adds content for class 1 syllabus
2020-02-04 adds video to marquee page
2020-02-04 adds instructions for student license
2020-02-08 adds programming-jig finish to class 2 homework
2020-02-08 adds req for 3.3mm mounting hole on marquee letter
2020-02-13 adds student links for 2020
2020-02-14 add slink to capsense library
2020-02-14 adds another student link
2020-02-20 specifies homework for class 4
2020-02-20 updates class-4 contents
2020-02-21 updates 1 student link
2020-02-21 adds link to bantam setup guide in syllabus
2020-03-06 syllabus materials for class 6
2020-03-06 adds materials from class 5
2020-03-06 updates student link
2020-03-13 updates JLINK and ATSAMD11C14A instructions
2020-03-14 adds links to videos on syllabus
2020-03-27 adds remote modifactions for class 8
2020-03-28 adds real-world Eagle guide
2020-03-30 fixes real-world guide title
2020-03-31 adds acid-etching guide
2020-04-03 adds image of cutting outline/holes before etching
2020-04-03 adds guides for class 9
2020-04-03 adds links to guides for class 9
2020-04-07 soldermask notes
2020-04-09 updates class 10 syllabus
2020-05-03 Create CNAME
2021-10-27 adds Spring 2020 archive
2021-10-27 changes link for syllabus to 2021
2021-10-27 updates syllabus skeleton for 2021
2021-10-28 text is over images
2021-11-03 adds 2021 class dates to syllabus
2022-01-23 updates Things links for 2022
2022-01-25 adds week1 homework
2022-01-25 adds presentation and image to week-1
2022-01-25 Spring '22
2022-01-29 udpates for class-2
2022-01-29 adds micro requirement for class 2
2022-01-29 adds male header-pins to class 2 items
2022-02-07 adds student blog links
2022-02-07 updates class-3 homework on syllabus page
2022-02-08 adds 4x5in spec to copper boards
2022-02-16 link to fusion 360 board outline guide; adds more student links
2022-02-16 adds images for scour pads and solder paste
2022-02-16 adds links to bantam guides
2022-03-01 adds voltage/current presentations to syllabus
2022-03-07 updates class-6
2022-03-21 updates for class 7 syllabus
2022-03-21 updates ordering links for recommended parts
2022-03-27 fix github links to example schematics
2022-04-18 8-minute beta presentation
2022-04-18 adds links for class 11
2024-01-04 archive spring 2022
2024-01-04 rename 2022 to 2024
2024-01-04 update syllabus page to 2024
2024-01-04 fix merge mistake
2024-01-20 add individual rules-of-electricity slide links
2024-02-17 marquee soldering due week 6; show marquee schematics
2024-02-17 add link to example schematics on syllabus homework section
2024-02-20 adds rescheduled label next to rescheduled classes
2024-02-23 remove Tuesday class from syllabus
2024-03-15 rearrange classes for 2x reschedules

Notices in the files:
parts and their libraries:
SparkFun-Resistors: Licensing: Creative Commons ShareAlike 4.0 International - https://creativecommons.org/licenses/by-sa/4.0
microbuilder: This work is placed in the public domain, and may be freely used for commercial and non-commercial work with the following conditions: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
